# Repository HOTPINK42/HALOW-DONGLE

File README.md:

# HALOW-DONGLE
building a halow usb dongle using mm8108

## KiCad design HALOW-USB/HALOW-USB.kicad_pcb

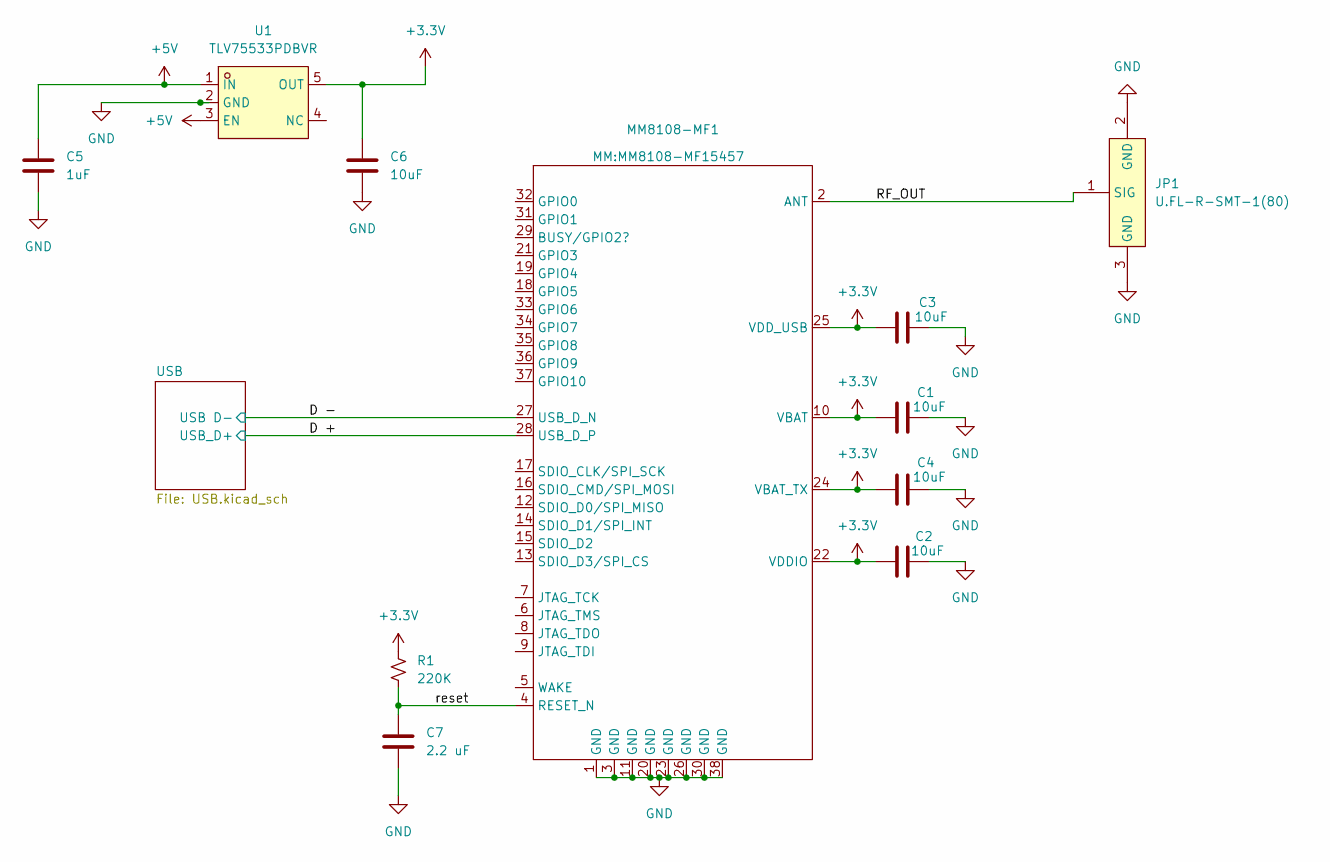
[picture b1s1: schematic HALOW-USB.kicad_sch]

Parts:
C1, C2, C3, C4, C6: 10uF; C_0603_1608Metric_Pad1.08x0.95mm_HandSolder
C5: 1uF; C_0603_1608Metric_Pad1.08x0.95mm_HandSolder
C7: 2.2 uF; C_0603_1608Metric_Pad1.08x0.95mm_HandSolder
JP1: U.FL-R-SMT-1(80); RF-SMD_FRF05002-JSS103M; LCSC Part C88374
MM8108-MF1: MM8108-MF15457
R1: 220K; R_0603_1608Metric_Pad0.98x0.95mm_HandSolder
U1: TLV75533PDBVR; SOT-23-5_L3.0-W1.7-P0.95-LS2.8-BR; LCSC Part C404027

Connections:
+3.3V: C1.1, C2.1, C3.1, C4.2, C6.1, MM8108-MF1.10 (VBAT), MM8108-MF1.22 (VDDIO), MM8108-MF1.24 (VBAT_TX), MM8108-MF1.25 (VDD_USB), R1.1, U1.5 (OUT)
+5V: C5.1, U1.1 (IN), U1.3 (EN); also elsewhere on the board
/D +: MM8108-MF1.28 (USB_D_P); also elsewhere on the board
/D -: MM8108-MF1.27 (USB_D_N); also elsewhere on the board
/RF_OUT: JP1.1 (SIG), MM8108-MF1.2 (ANT)
/reset: C7.1, MM8108-MF1.4 (RESET_N), R1.2
GND: C1.2, C2.2, C3.2, C4.1, C5.2, C6.2, C7.2, JP1.2 (GND), JP1.3 (GND), MM8108-MF1.1 (GND), MM8108-MF1.3 (GND), MM8108-MF1.11 (GND), MM8108-MF1.20 (GND), MM8108-MF1.23 (GND), MM8108-MF1.26 (GND), MM8108-MF1.30 (GND), MM8108-MF1.38 (GND), U1.2 (GND); also elsewhere on the board

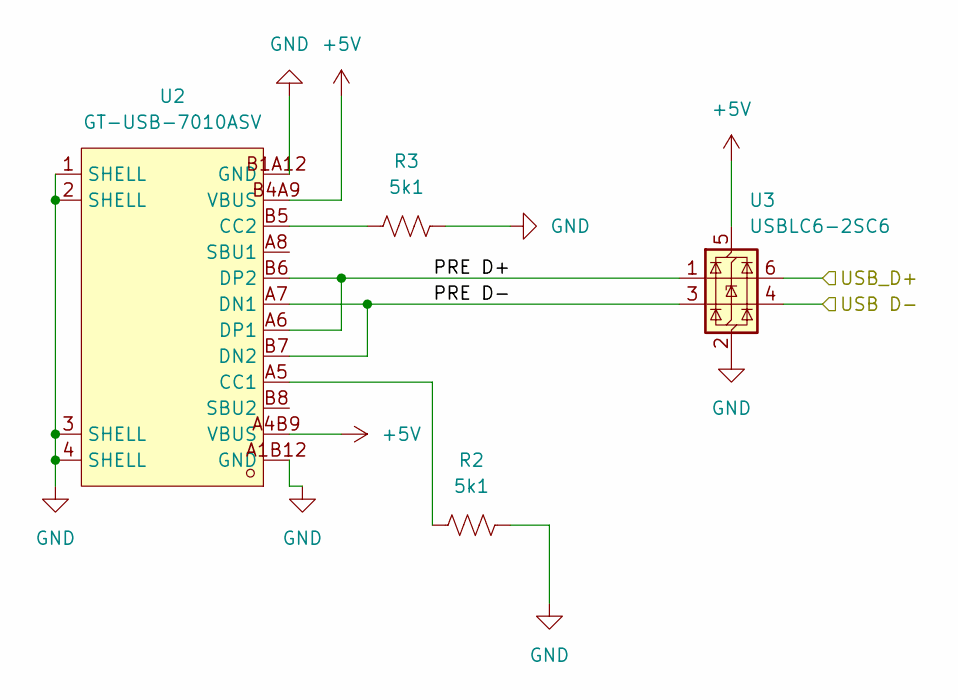
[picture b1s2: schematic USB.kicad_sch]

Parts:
R2, R3: 5k1; R_0603_1608Metric_Pad0.98x0.95mm_HandSolder
U2: GT-USB-7010ASV; USB-C-SMD_G-SWITCH_GT-USB-7010ASV; LCSC Part C2988369
U3: USBLC6-2SC6; SOT-23-6

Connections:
+5V: U2.A4B9 (VBUS), U2.B4A9 (VBUS), U3.5 (VBUS); also elsewhere on the board
/D +: U3.6 (I/O1); also elsewhere on the board
/D -: U3.4 (I/O2); also elsewhere on the board
/USB/PRE D+: U2.A6 (DP1), U2.B6 (DP2), U3.1 (I/O1)
/USB/PRE D-: U2.A7 (DN1), U2.B7 (DN2), U3.3 (I/O2)
GND: R2.2, R3.2, U2.1 (SHELL), U2.2 (SHELL), U2.3 (SHELL), U2.4 (SHELL), U2.A1B12 (GND), U2.B1A12 (GND), U3.2 (GND); also elsewhere on the board
unnamed: R2.1, U2.A5 (CC1)
unnamed: R3.1, U2.B5 (CC2)

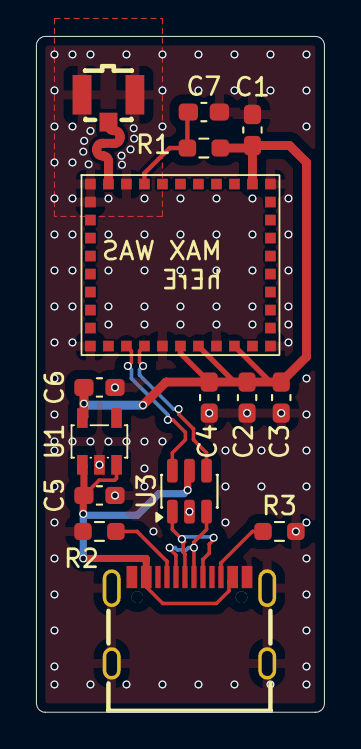
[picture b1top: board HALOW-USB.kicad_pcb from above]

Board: 2 copper layers, 16.0 x 37.5 mm, 15 parts (0 on the bottom side), 11 nets.

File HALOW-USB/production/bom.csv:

Designator,Footprint,Quantity,Value,LCSC Part #
"C1, C2, C3, C4, C6",0603,5,10uF,
C5,0603,1,1uF,
C7,0603,1,2.2 uF,
JP1,RF-SMD_FRF05002-JSS103M,1,U.FL-R-SMT-1(80),C88374
MM8108-MF1,MM8108-MF15457,1,~,
R1,0603,1,220K,
"R2, R3",0603,2,5k1,
U1,SOT-23-5_L3.0-W1.7-P0.95-LS2.8-BR,1,TLV75533PDBVR,C404027
U2,USB-C-SMD_G-SWITCH_GT-USB-7010ASV,1,GT-USB-7010ASV,C2988369
U3,SOT-23-6,1,USBLC6-2SC6,

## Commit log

2025-12-17 Moved files from old repo
2025-12-17 trace work
2025-12-22 mfg files added
2025-12-31 added 5v enable and stp export
2026-01-09 test
